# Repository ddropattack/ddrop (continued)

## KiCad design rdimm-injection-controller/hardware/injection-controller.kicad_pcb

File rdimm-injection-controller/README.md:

# RDIMM DDR5 Injection controller
Hardware design files and firmware for the injection controller PCB that
controls the DDR5 RDIMM interposer by using a Teensy 4.1 microcontroller. This is
a 2-layer PCB.

This is v2 of the [REFault injection controller](https://github.com/refault-artifacts/injection-controller).
The versions are mostly compatible; some firmware changes may be necessary.

## Design
The schematic and PCB was designed in KiCAD. Open `hardware/injection-controller.kicad_pro` in KiCAD 9.0.2 or later to view the design files.
From there, you should be able to select the schematic and PCB layout.
You can find a BOM spreadsheet in `docs/bom`.

For convenience, you can also find a PDF version of the schematic in `docs/schematics.pdf`.

## Features

 - **Relay**: Meant for emulating the power button of the system-under-test for fully automated test setups.
 - **Button**: Button can be configured with a jumper as programmable user button or hard-wired to control the relay.
 - **Ethernet**: RJ45 Jack connected to the Ethernet header pins of the Teensy.
 - **Pluggable Teensy**: The Teensy microcontroller board is meant to be
 attached to the PCB by using headers, allowing for easy replacement and
 swapping of microcontroller.
 - **Status LED**: One power LED, one relay LED, and one user controllable LED on the board.
- **Flat flex connector**: By using a suitable flat flex cable, the controller
 can be easily connected to the DDR5 fault injector interposer.

## Manufacturing
The PCBs were manufactured by JLCPCB and were assembled by hand.
It is reasonable to also order a SMT stencil so soldering is easier.
The Gerber files needed for manufacturing are located at hardware/output.

### Manufactoring options
| Option  | Value   |
|---------|---------|
| Layers  |   2     |
| Dimension | 61 mm* 50.3 mm |
| Product Type | Industrial/Consumer electronics |
| Different Design | 1|
| Delivery Format | Single PCB|
| PCB Thickness | 1.6|
| Impedance Control | no|
| Layer Sequence ||
| PCB Color | Green|
| Silkscreen | White|
| Via Covering | Tented|
| Surface Finish | LeadFree HASL|
| Deburring/Edge rounding | No|
| Outer Copper Weight | 1|
| Gold Fingers | No|
| Flying Probe Test | Fully Test|
| Castellated Holes | no|
| Remove Order Number | No|
| 4-Wire Kelvin Test | No|
| Material Type | FR4-Standard TG 135-140|
| Paper between PCBs | No|
| Appearance Quality | IPC Class 2 Standard|
| Confirm Production file | No|
| Silkscreen Technology | Ink-jet/Screen Printing Silkscreen|
| Package Box | With JLCPCB logo |

## Assembly
Assembly can be done manually using a stencil, some solder paste and a hot air gun.

## License
Some parts of the PCB may be subject to copyright of third parties 
(e.g. 3D models provided by manufacturer).
Otherwise, the design is released under MIT License.

The KiCad symbol and footprint libraries for the Teensy microcontroller 
are taken from [here](https://github.com/XenGi/teensy_library) 
and [here](https://github.com/XenGi/teensy.pretty), respectively (MIT License).

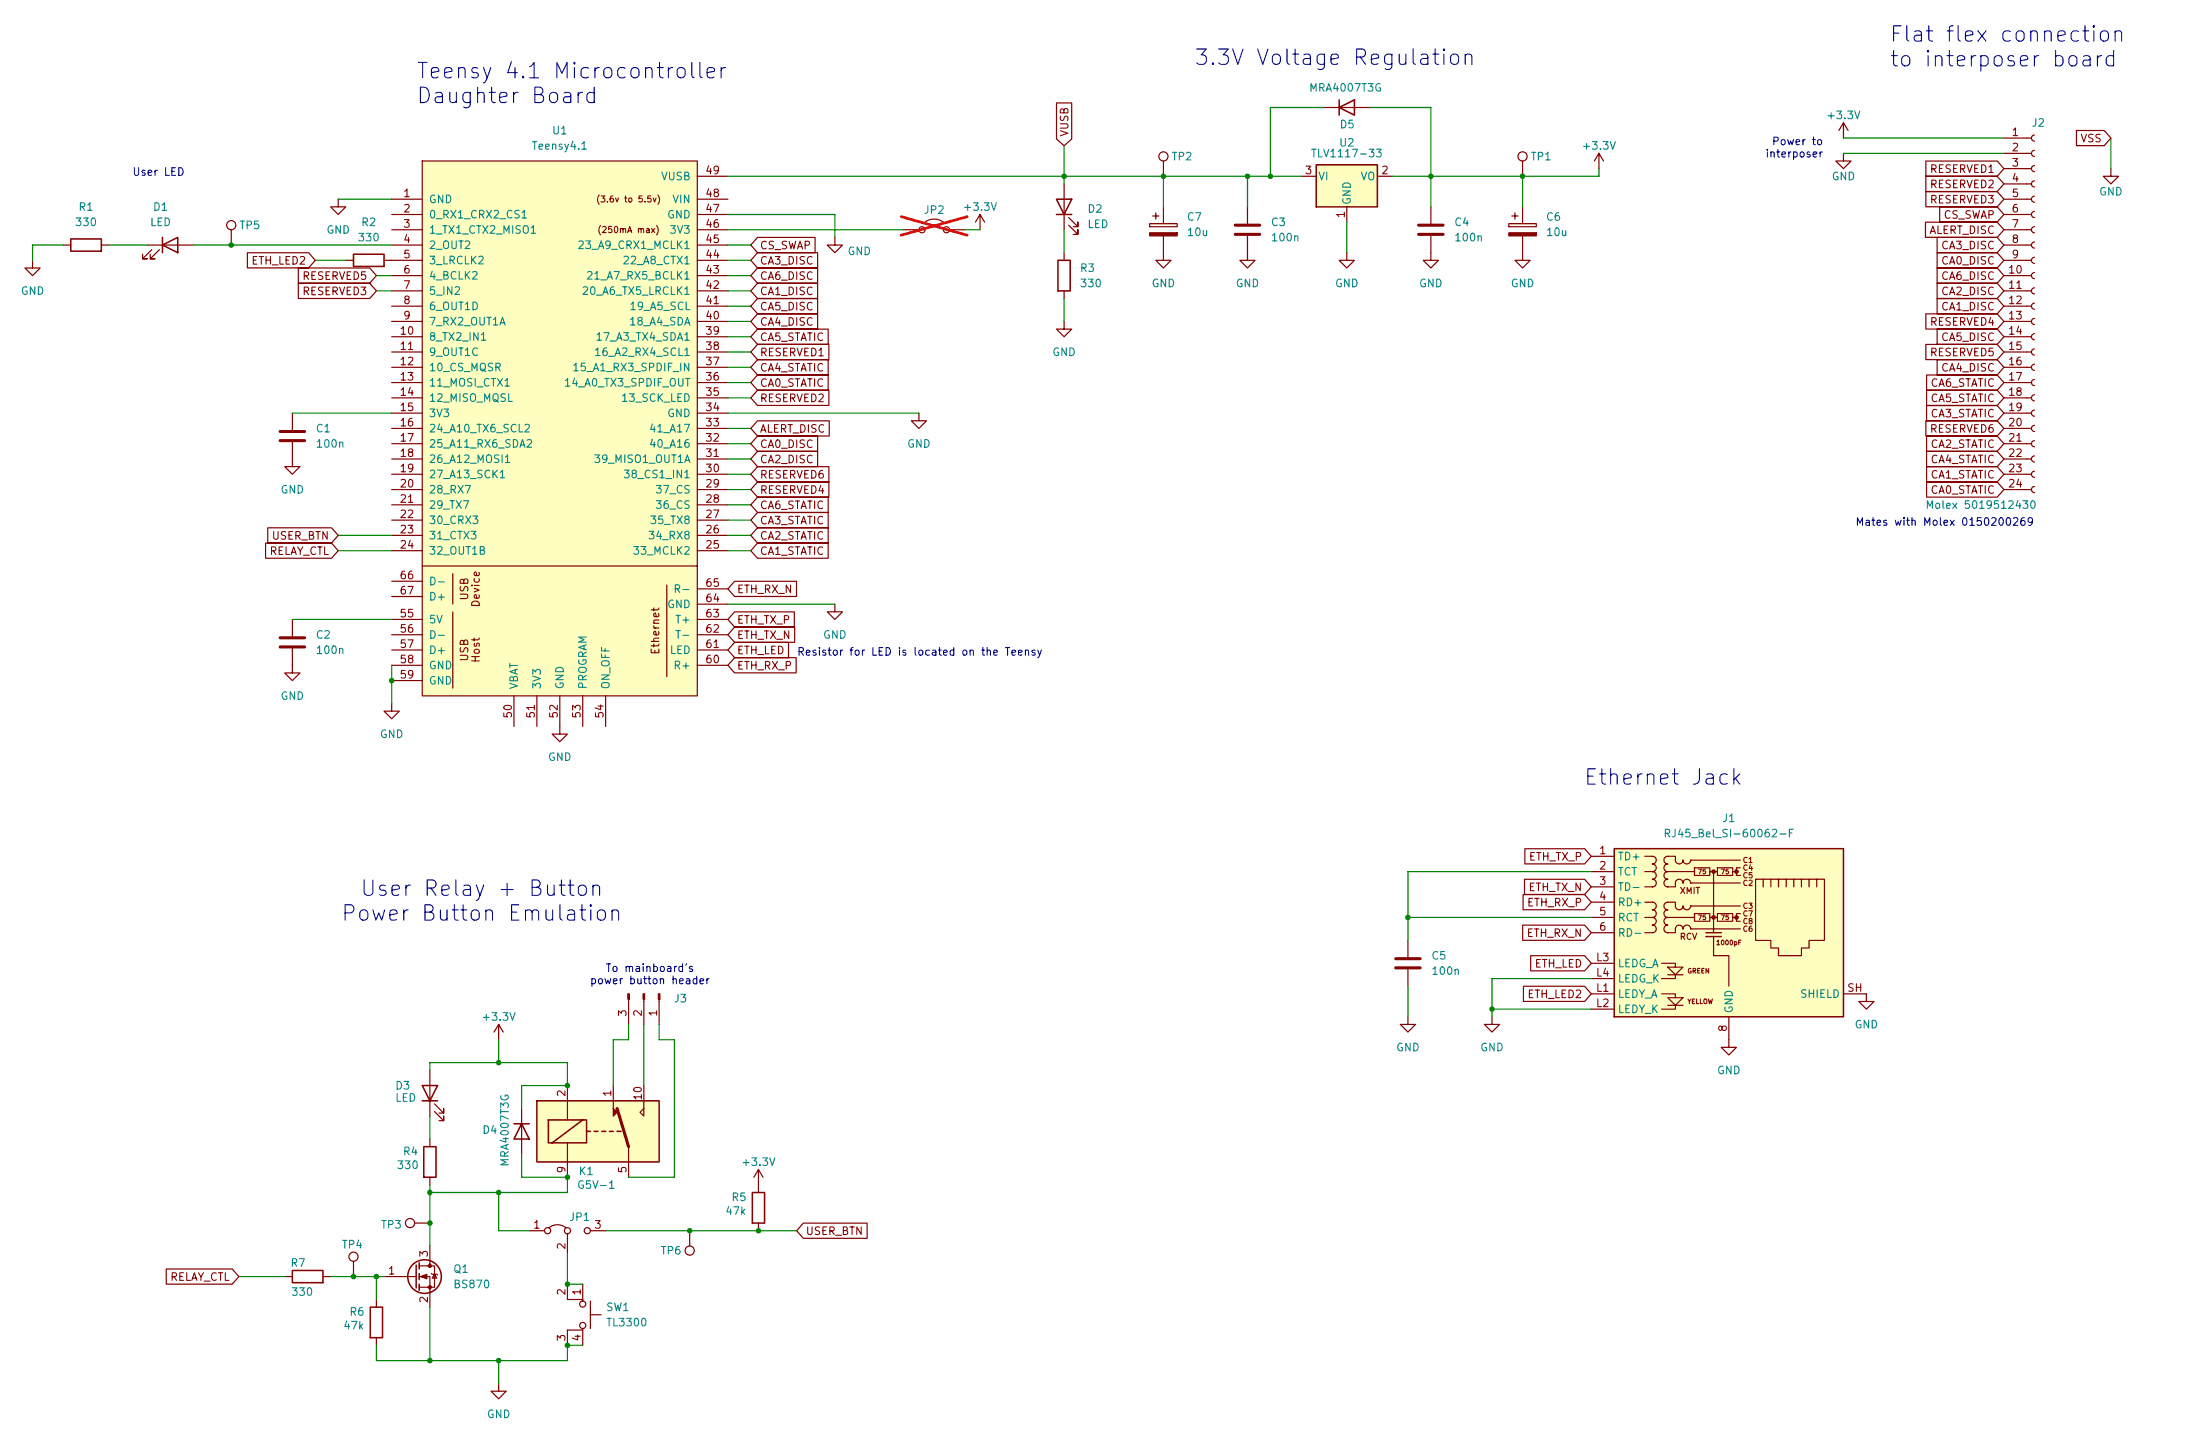
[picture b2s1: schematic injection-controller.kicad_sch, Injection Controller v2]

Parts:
C1, C2, C3, C4, C5: 100n; C_0603_1608Metric
C6, C7: 10u; CP_Elec_5x5.8
D1, D2, D3: LED; LED_0805_2012Metric
D4, D5: MRA4007T3G; D_SMA
J1: RJ45_Bel_SI-60062-F; 480251090
J2: Molex 5019512430; 5019512430
J3: Conn_01x03_Pin; PinHeader_1x03_P2.54mm_Vertical
JP1: Jumper_3_Bridged12; PinHeader_1x03_P2.54mm_Vertical
JP2: Jumper_2_Open; PinHeader_1x02_P2.54mm_Vertical; not fitted
K1: G5V-1; Relay_SPDT_Omron_G5V-1
Q1: BS870; SOT-23
R1, R2, R3, R4, R7: 330; R_0603_1608Metric
R5, R6: 47k; R_0603_1608Metric
SW1: TL3300
TP1, TP2, TP3, TP4, TP5, TP6: TestPoint; TestPoint_Keystone_5000-5004_Miniature
U1: Teensy4.1; Teensy41
U2: TLV1117-33; SOT-223-3_TabPin2

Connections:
+3.3V: C4.1, C6.1, D3.2 (A), D4.1 (K), D5.2 (A), J2.1, JP2.2 (B), K1.2, R5.1, TP1.1, U2.2 (VO)
ALERT_DISC: J2.7, U1.33 (41_A17)
CA0_DISC: J2.9, U1.32 (40_A16)
CA0_STATIC: J2.24, U1.36 (14_A0_TX3_SPDIF_OUT)
CA1_DISC: J2.12, U1.42 (20_A6_TX5_LRCLK1)
CA1_STATIC: J2.23, U1.25 (33_MCLK2)
CA2_DISC: J2.11, U1.31 (39_MISO1_OUT1A)
CA2_STATIC: J2.21, U1.26 (34_RX8)
CA3_DISC: J2.8, U1.44 (22_A8_CTX1)
CA3_STATIC: J2.19, U1.27 (35_TX8)
CA4_DISC: J2.16, U1.40 (18_A4_SDA)
CA4_STATIC: J2.22, U1.37 (15_A1_RX3_SPDIF_IN)
CA5_DISC: J2.14, U1.41 (19_A5_SCL)
CA5_STATIC: J2.18, U1.39 (17_A3_TX4_SDA1)
CA6_DISC: J2.10, U1.43 (21_A7_RX5_BCLK1)
CA6_STATIC: J2.17, U1.28 (36_CS)
CS_SWAP: J2.6, U1.45 (23_A9_CRX1_MCLK1)
ETH_LED: J1.L3 (LEDG_A), U1.61 (LED)
ETH_LED2: J1.L1 (LEDY_A), R2.1
ETH_RX_N: J1.6 (RD-), U1.65 (R-)
ETH_RX_P: J1.4 (RD+), U1.60 (R+)
ETH_TX_N: J1.3 (TD-), U1.62 (T-)
ETH_TX_P: J1.1 (TD+), U1.63 (T+)
unnamed: C1.1, U1.15 (3V3)
unnamed: D1.2 (A), TP5.1, U1.4 (2_OUT2)
unnamed: D1.1 (K), R1.2
unnamed: D2.1 (K), R3.1
unnamed: D3.1 (K), R4.1
unnamed: D4.2 (A), JP1.1 (A), K1.9, Q1.3 (D), R4.2, TP3.1
unnamed: C5.1, J1.2 (TCT), J1.5 (RCT)
unnamed: J3.1, K1.5, K1.6
unnamed: J3.2, K1.10
unnamed: J3.3, K1.1
unnamed: JP1.2 (C), SW1.1, SW1.2
unnamed: JP2.1 (A), U1.46 (3V3)
unnamed: Q1.1 (G), R6.1, R7.2, TP4.1
unnamed: R2.2, U1.5 (3_LRCLK2)
unnamed: C2.1, U1.55 (5V)
RELAY_CTL: R7.1, U1.24 (32_OUT1B)
RESERVED1: J2.3, U1.38 (16_A2_RX4_SCL1)
RESERVED2: J2.4, U1.35 (13_SCK_LED)
RESERVED3: J2.5, U1.7 (5_IN2)
RESERVED4: J2.13, U1.29 (37_CS)
RESERVED5: J2.15, U1.6 (4_BCLK2)
RESERVED6: J2.20, U1.30 (38_CS1_IN1)
USER_BTN: JP1.3 (B), R5.2, TP6.1, U1.23 (31_CTX3)
VSS: C1.2, C2.2, C3.2, C4.2, C5.2, C6.2, C7.2, J1.8 (GND), J1.L2 (LEDY_K), J1.L4 (LEDG_K), J1.SH (SHIELD), J2.2, Q1.2 (S), R1.1, R3.2, R6.2, SW1.3 (K), SW1.4 (A), U1.1 (GND), U1.34 (GND), U1.47 (GND), U1.52 (GND), U1.58 (GND), U1.59 (GND), U1.64 (GND), U2.1 (GND)
VUSB: C3.1, C7.1, D2.2 (A), D5.1 (K), TP2.1, U1.49 (VUSB), U2.3 (VI)

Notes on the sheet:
To mainboard's power button header
Mates with Molex 0150200269
Power to interposer
Flat flex connection to interposer board
User Relay + Button Power Button Emulation
User LED
3.3V Voltage Regulation
Resistor for LED is located on the Teensy
Ethernet Jack
Teensy 4.1 Microcontroller Daughter Board

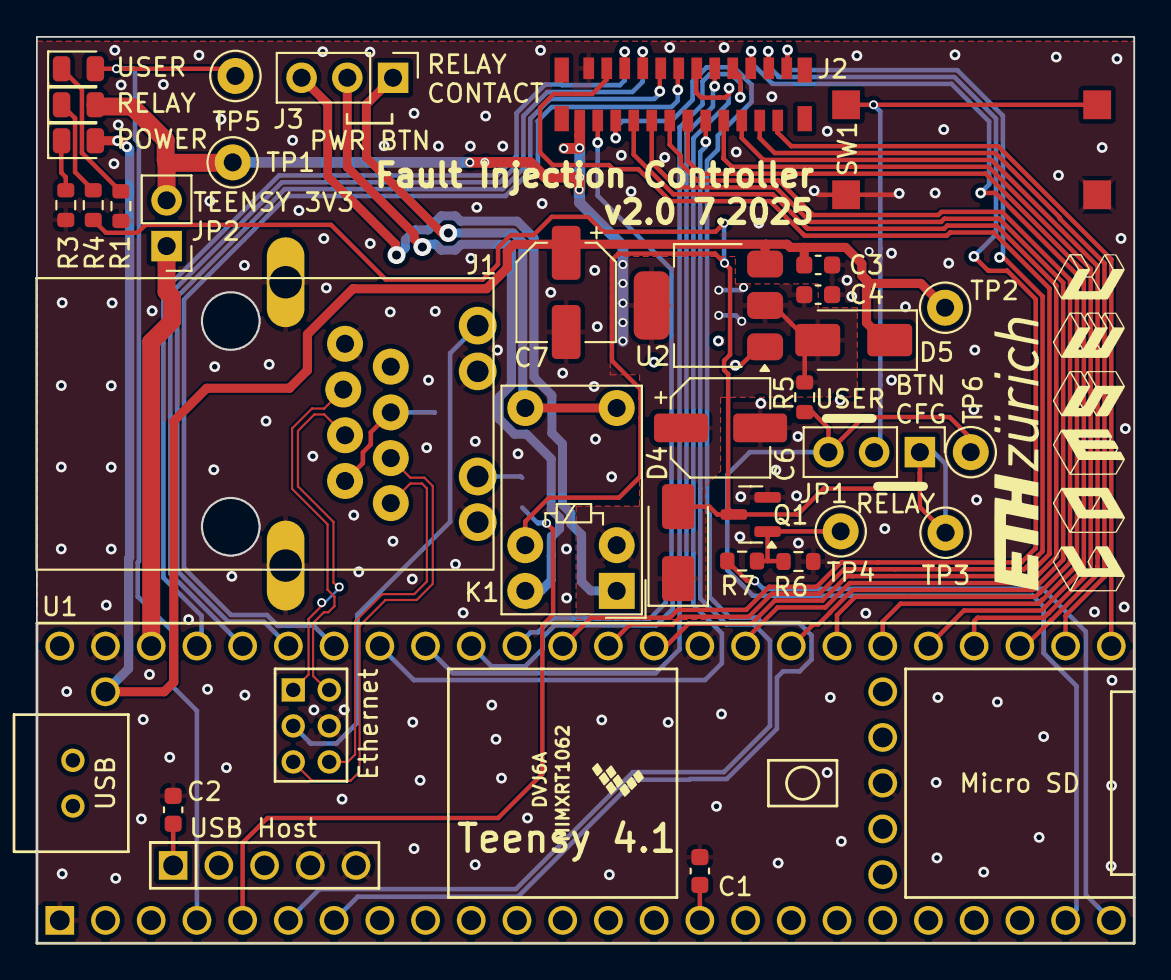
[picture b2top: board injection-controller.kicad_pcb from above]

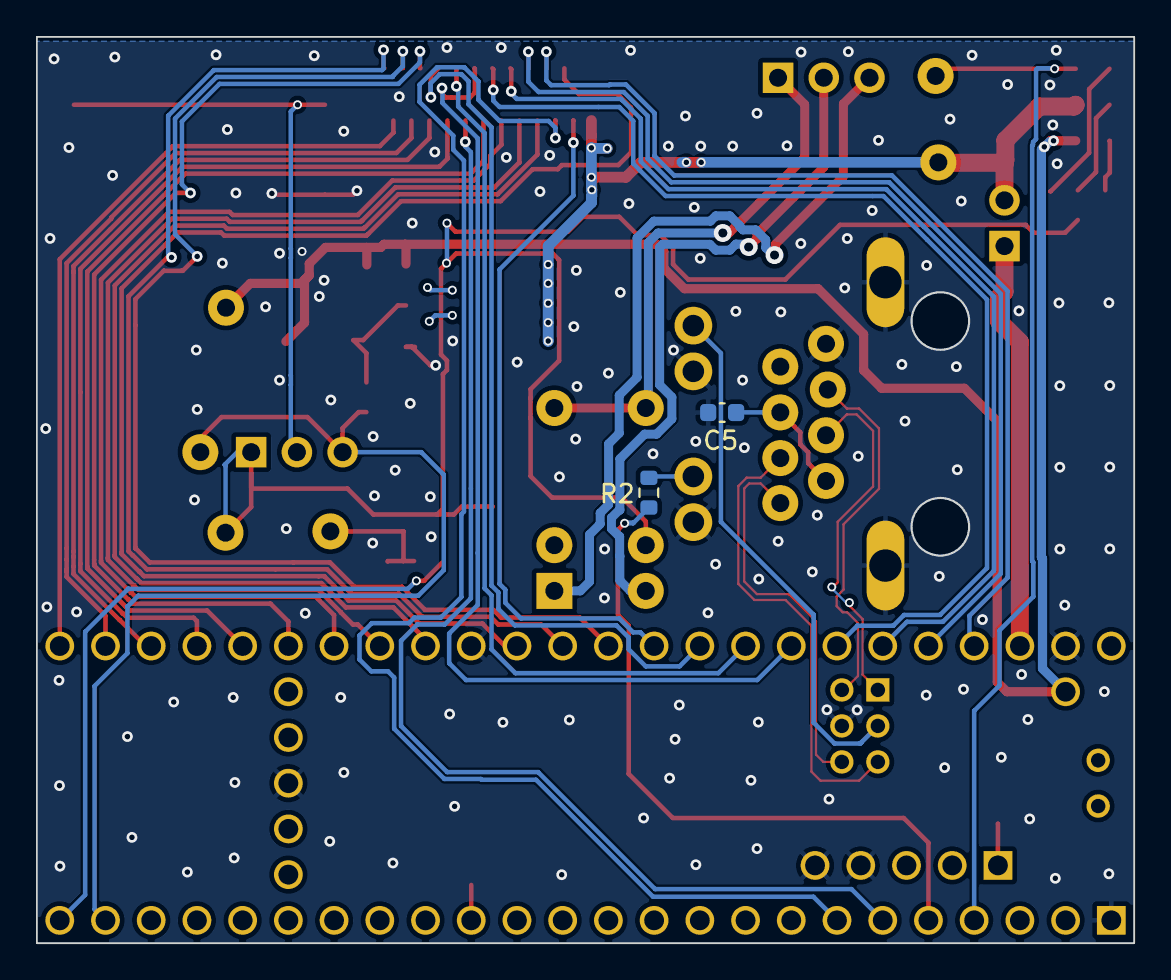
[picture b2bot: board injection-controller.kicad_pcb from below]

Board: 2 copper layers, 61.0 x 50.3 mm, 35 parts (2 on the bottom side), 48 nets.

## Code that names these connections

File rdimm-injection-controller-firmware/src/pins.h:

/* GPIO pin definitions */
#define PIN_LED_ETH_RIGHT 3
#define PIN_LED_STATUS 2
#define PIN_PWR_BTN 32

#define PIN_CS_SWAP 23
#define PIN_ALERT_DISC 41
#define PIN_CA3_DISC 22
#define PIN_CA0_DISC 40
#define PIN_CA6_DISC 21
#define PIN_CA2_DISC 39
#define PIN_CA1_DISC 20
#define PIN_CA5_DISC 19
#define PIN_CA4_DISC 18
#define PIN_CA6_STATIC 36
#define PIN_CA5_STATIC 17
#define PIN_CA3_STATIC 35
#define PIN_CA2_STATIC 34
#define PIN_CA4_STATIC 15
#define PIN_CA1_STATIC 33
#define PIN_CA0_STATIC 14

int init_gpios();
